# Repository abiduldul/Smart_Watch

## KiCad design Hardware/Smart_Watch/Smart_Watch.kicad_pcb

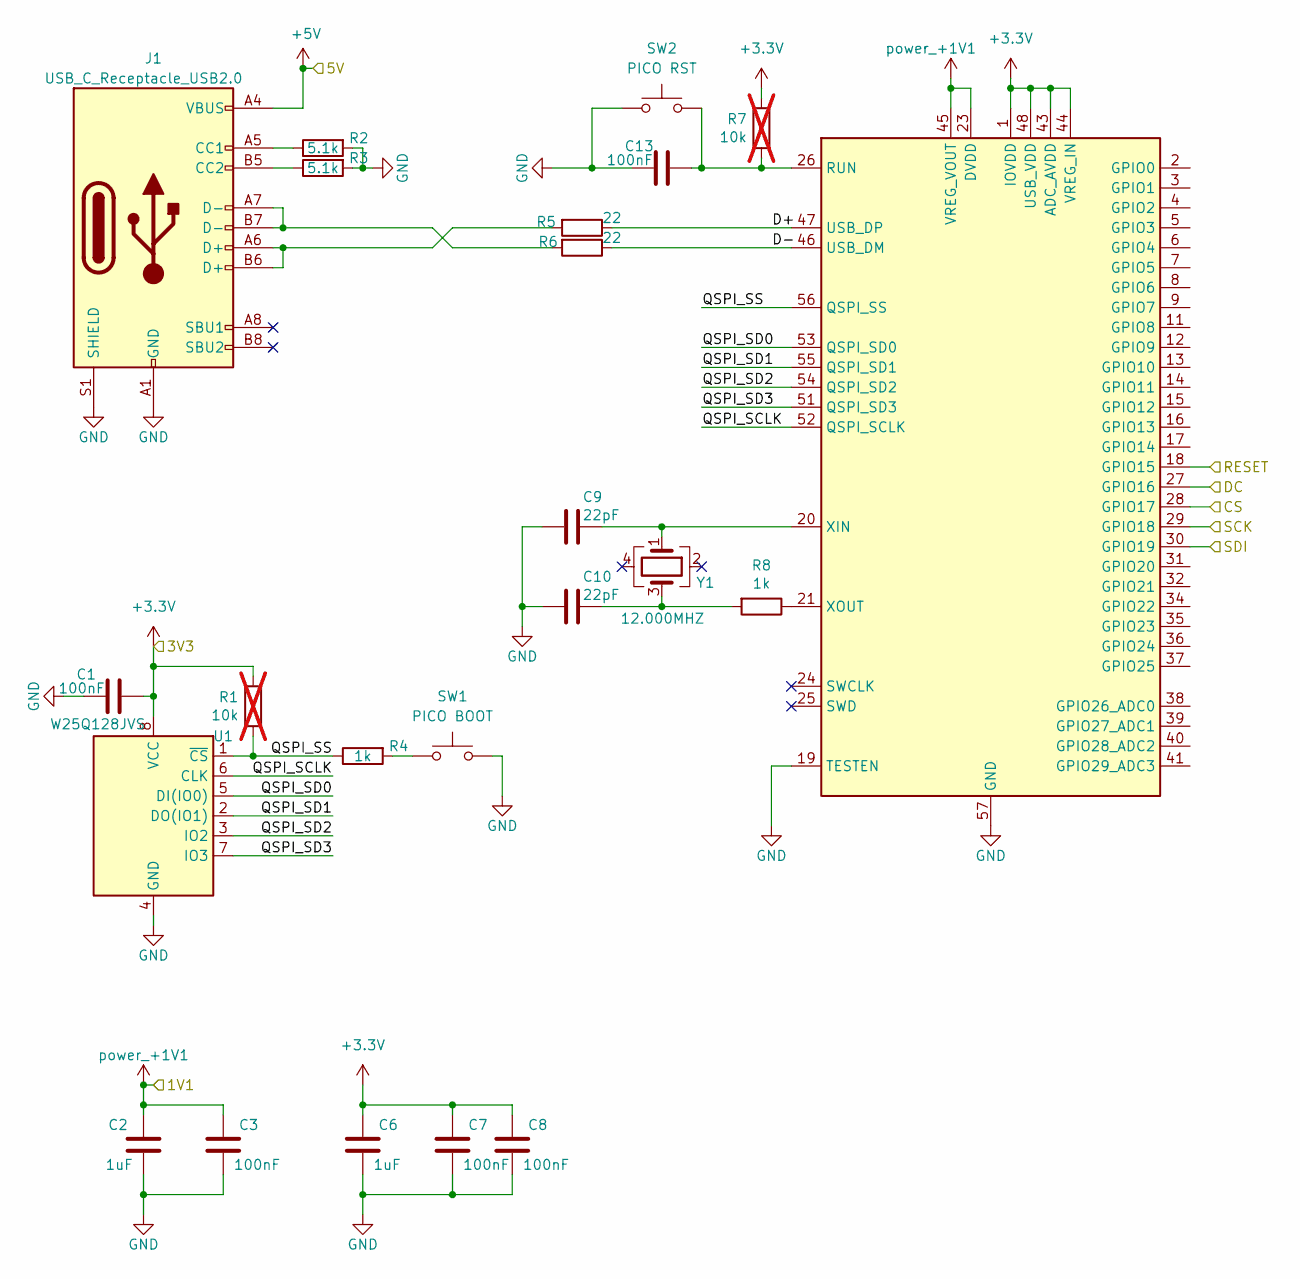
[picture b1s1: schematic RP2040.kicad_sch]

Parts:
C1, C3, C7, C8, C13: 100nF; C_0402_1005Metric; JLCPCB Part#(optional) C1525
C2, C6: 1uF; C_0402_1005Metric; JLCPCB Part#(optional) C52923
C9, C10: 22pF; C_0402_1005Metric; JLCPCB Part#(optional) C1555
J1: USB_C_Receptacle_USB2.0; USB_C_Receptacle_HRO_TYPE-C-31-M-12; JLCPCB Part#(optional) C165948
R1, R7: 10k; R_0402_1005Metric; JLCPCB Part#(optional) C25744; not fitted
R2, R3: 5.1k; R_0402_1005Metric; JLCPCB Part#(optional) C25905
R4, R8: 1k; R_0402_1005Metric; JLCPCB Part#(optional) C11702
R5, R6: 22; R_0402_1005Metric; JLCPCB Part#(optional) C25092
SW1: PICO BOOT; SW_SPST_B3U-1000P; JLCPCB Part#(optional) C231329
SW2: PICO RST; SW_SPST_B3U-1000P; JLCPCB Part#(optional) C231329
U1: W25Q128JVS; SOIC-8_5.23x5.23mm_P1.27mm; JLCPCB Part#(optional) C97521
U2: RP2040; QFN-56-1EP_7x7mm_P0.4mm_EP3.2x3.2mm; JLCPCB Part#(optional) C2040
Y1: 12.000MHZ; Crystal_SMD_Abracon_ABM10-4Pin_2.5x2.0mm; JLCPCB Part#(optional) C284155

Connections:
+3.3V: C1.1, C6.1, C7.1, C8.1, R1.1, R7.1, U1.8 (VCC), U2.1 (IOVDD), U2.10 (IOVDD), U2.22 (IOVDD), U2.33 (IOVDD), U2.42 (IOVDD), U2.43 (ADC_AVDD), U2.44 (VREG_IN), U2.48 (USB_VDD), U2.49 (IOVDD); also elsewhere on the board
+5V: J1.A4 (VBUS), J1.A9 (VBUS), J1.B4 (VBUS), J1.B9 (VBUS); also elsewhere on the board
/RP2040/CS: U2.28 (GPIO17); also elsewhere on the board
/RP2040/D+: R5.1, U2.47 (USB_DP)
/RP2040/D-: R6.1, U2.46 (USB_DM)
/RP2040/DC: U2.27 (GPIO16); also elsewhere on the board
/RP2040/QSPI_SCLK: U1.6 (CLK), U2.52 (QSPI_SCLK)
/RP2040/QSPI_SD0: U1.5 (DI(IO0)), U2.53 (QSPI_SD0)
/RP2040/QSPI_SD1: U1.2 (DO(IO1)), U2.55 (QSPI_SD1)
/RP2040/QSPI_SD2: U1.3 (IO2), U2.54 (QSPI_SD2)
/RP2040/QSPI_SD3: U1.7 (IO3), U2.51 (QSPI_SD3)
/RP2040/QSPI_SS: R1.2, R4.1, U1.1 (~CS), U2.56 (QSPI_SS)
/RP2040/RESET: U2.18 (GPIO15); also elsewhere on the board
/RP2040/SCK: U2.29 (GPIO18); also elsewhere on the board
/RP2040/SDI: U2.30 (GPIO19); also elsewhere on the board
GND: C1.2, C2.2, C3.2, C6.2, C7.2, C8.2, C9.2, C10.2, C13.2, J1.A1 (GND), J1.A12 (GND), J1.B1 (GND), J1.B12 (GND), J1.S1 (SHIELD), R2.2, R3.2, SW1.1, SW2.2, U1.4 (GND), U2.19 (TESTEN), U2.57 (GND); also elsewhere on the board
unnamed: C10.1, R8.2, Y1.3
unnamed: J1.A5 (CC1), R2.1
unnamed: J1.B5 (CC2), R3.1
unnamed: J1.A6 (D+), J1.B6 (D+), R5.2
unnamed: J1.A7 (D-), J1.B7 (D-), R6.2
unnamed: R4.2, SW1.2
unnamed: C13.1, R7.2, SW2.1, U2.26 (RUN)
unnamed: C9.1, U2.20 (XIN), Y1.1
unnamed: R8.1, U2.21 (XOUT)
power_+1V1: C2.1, C3.1, U2.23 (DVDD), U2.45 (VREG_VOUT), U2.50 (DVDD); also elsewhere on the board

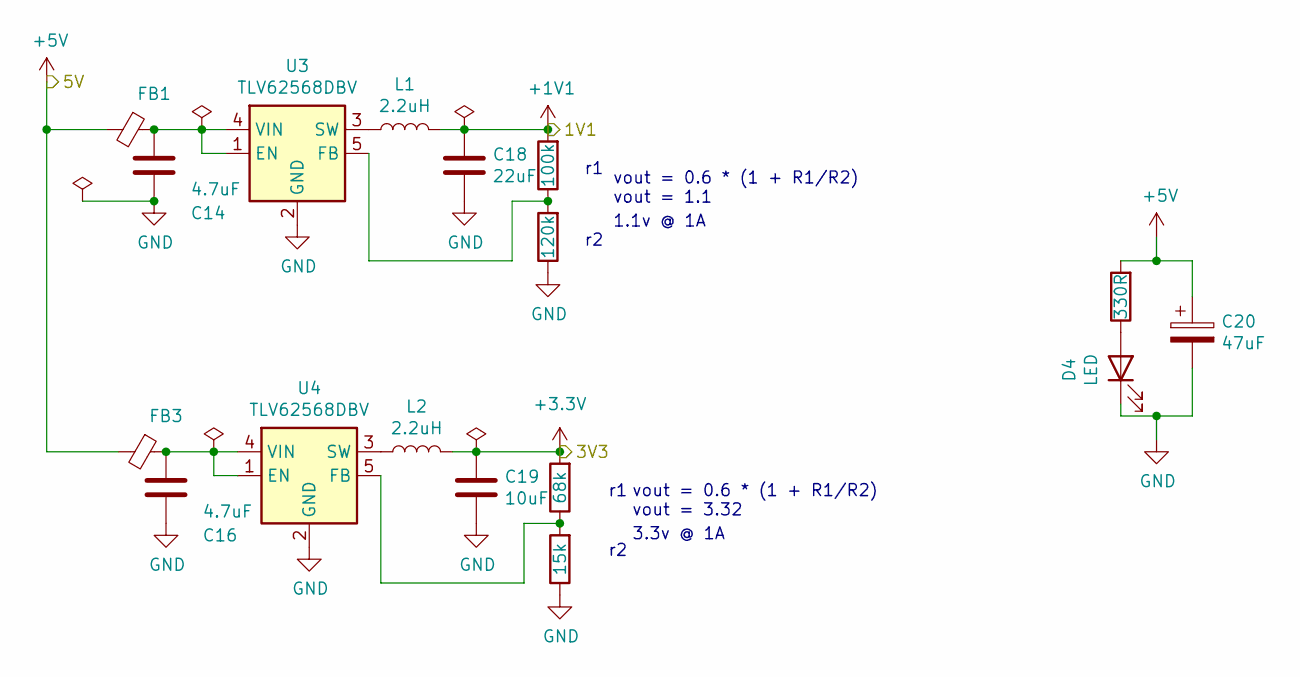
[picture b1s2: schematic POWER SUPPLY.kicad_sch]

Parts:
C14, C16: 4.7uF; C_0402_1005Metric; JLCPCB Part#(optional) C23733
C18: 22uF; C_0603_1608Metric; JLCPCB Part#(optional) C59461
C19: 10uF; C_0603_1608Metric; JLCPCB Part#(optional) C19702
C20: 47uF; CP_EIA-3216-18_Kemet-A; JLCPCB Part#(optional) C129570
D4: LED; LED_0603_1608Metric; JLCPCB Part#(optional) C2286
FB1, FB3: Ferrite_Bead_Small; L_0805_2012Metric; JLCPCB Part#(optional) C1015
L1, L2: 2.2uH; L_Cenker_CKCS3015; JLCPCB Part#(optional) C43389
R16: 100k; R_0402_1005Metric; JLCPCB Part#(optional) C25741
R17: 120k; R_0402_1005Metric; JLCPCB Part#(optional) C25750
R18: 68k; R_0402_1005Metric; JLCPCB Part#(optional) C36871
R19: 15k; R_0402_1005Metric; JLCPCB Part#(optional) C25756
R20: 330R; R_0402_1005Metric; JLCPCB Part#(optional) C25104
U3, U4: TLV62568DBV; SOT-23-5; JLCPCB Part#(optional) C163219

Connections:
+3.3V: C19.1, L2.1, R18.2; also elsewhere on the board
+5V: C20.1, FB1.2, FB3.2, R20.2; also elsewhere on the board
GND: C14.2, C16.2, C18.2, C19.2, C20.2, D4.1 (K), R17.1, R19.1, U3.2 (GND), U4.2 (GND); also elsewhere on the board
unnamed: D4.2 (A), R20.1
unnamed: C14.1, FB1.1, U3.1 (EN), U3.4 (VIN)
unnamed: R16.1, R17.2, U3.5 (FB)
unnamed: L1.1, U3.3 (SW)
unnamed: C16.1, FB3.1, U4.1 (EN), U4.4 (VIN)
unnamed: R18.1, R19.2, U4.5 (FB)
unnamed: L2.2, U4.3 (SW)
power_+1V1: C18.1, L1.2, R16.2; also elsewhere on the board

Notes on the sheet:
1.1v @ 1A
vout = 0.6 * (1 + R1/R2) vout = 3.32
vout = 0.6 * (1 + R1/R2) vout = 1.1
3.3v @ 1A

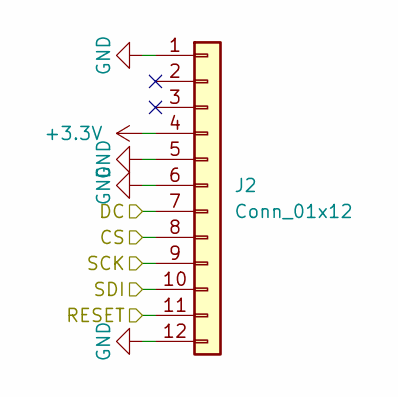
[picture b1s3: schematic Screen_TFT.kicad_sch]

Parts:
J2: Conn_01x12; GC9A01_Extended_FPC

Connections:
+3.3V: J2.4; also elsewhere on the board
/RP2040/CS: J2.8; also elsewhere on the board
/RP2040/DC: J2.7; also elsewhere on the board
/RP2040/RESET: J2.11; also elsewhere on the board
/RP2040/SCK: J2.9; also elsewhere on the board
/RP2040/SDI: J2.10; also elsewhere on the board
GND: J2.1, J2.5, J2.6, J2.12; also elsewhere on the board

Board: 2 copper layers, 41 parts (0 on the bottom side), 33 nets, no tracks yet.

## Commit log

2024-11-18 Initial design
2024-11-18 update layout pcb
2024-11-19 add screen
2024-11-19 update screen
